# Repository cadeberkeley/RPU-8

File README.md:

# RPU-8
8-Bit Retro Processing Unit

Started on breadboards, inspired by Ben Eater's 8-bit CPU.  I got it more or less working on breadboards, and I am currently designing PCBs to make it more permanent and hopefully solve any power distribution or connection issues with the breadboard design.  I have sketched out a modular stacking design, so it will be easier to swap out for larger instruction/data memory or a larger program counter if I so please.

I am using KiCAD for schematic and PCB design.  Planning to source PCBs from JLCPCB.

TODO: Add images of breadboard.

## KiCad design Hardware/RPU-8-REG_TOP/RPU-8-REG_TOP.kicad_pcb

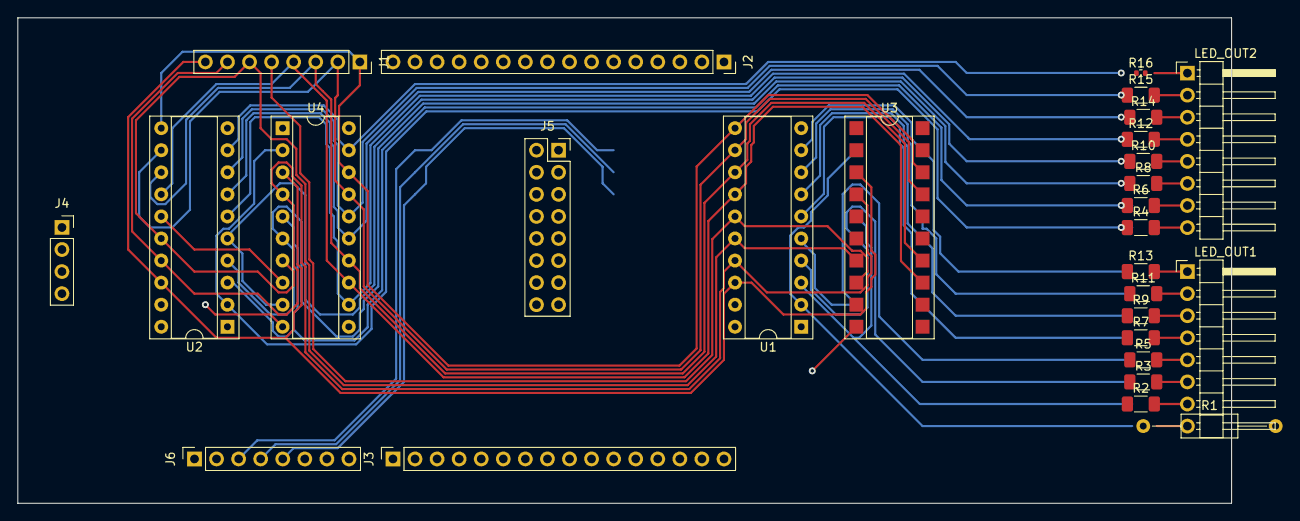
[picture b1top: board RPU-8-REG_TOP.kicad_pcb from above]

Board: 2 copper layers, 139.7 x 55.9 mm, 28 parts (0 on the bottom side), 47 nets.

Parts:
J1: DATA_BUS; PinSocket_1x08_P2.54mm_Vertical
J2: ADDR_BUS; PinSocket_1x16_P2.54mm_Vertical
J3: CTRL_BUS; PinSocket_1x16_P2.54mm_Vertical
J4: Conn_01x03_Female; PinSocket_1x04_P2.54mm_Vertical
J5: REG_CTRL; PinSocket_2x08_P2.54mm_Vertical
J6: INST_BITS; PinSocket_1x08_P2.54mm_Vertical
LED_OUT1, LED_OUT2: LEDs; PinHeader_1x08_P2.54mm_Horizontal
R1: 220Ω; R_Axial_DIN0207_L6.3mm_D2.5mm_P15.24mm_Horizontal
R2, R3, R4, R5, R6, R7, R8, R9, R10, R11, R12, R13, R14, R15: 220Ω; R_1206_3216Metric_Pad1.30x1.75mm_HandSolder
R16: 220Ω; R_0402_1005Metric
U1, U2: 74HC245; DIP-20_W7.62mm_Socket
U3: 74HC377; DIP-20_W7.62mm_SMDSocket_SmallPads
U4: 74HC377; DIP-20_W7.62mm_Socket

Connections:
+5V: J4.3, U1.1 (A->B), U1.20 (VCC), U2.1 (A->B), U2.20 (VCC), U3.20 (VCC), U4.20 (VCC)
CLK: J4.1, U3.11 (CP), U4.11 (CP)
D0: J1.1, U1.11 (B7), U2.11 (B7), U3.18 (D7), U4.18 (D7)
D1: J1.2, U1.12 (B6), U2.12 (B6), U3.17 (D6), U4.17 (D6)
D2: J1.3, U1.13 (B5), U2.13 (B5), U3.14 (D5), U4.14 (D5)
D3: J1.4, U1.14 (B4), U2.14 (B4), U3.13 (D4), U4.13 (D4)
D4: J1.5, U1.15 (B3), U2.15 (B3), U3.8 (D3), U4.8 (D3)
D5: J1.6, U1.16 (B2), U2.16 (B2), U3.7 (D2), U4.7 (D2)
D6: J1.7, U1.17 (B1), U2.17 (B1), U3.4 (D1), U4.4 (D1)
D7: J1.8, U1.18 (B0), U2.18 (B0), U3.3 (D0), U4.3 (D0)
GND: J4.2, U1.10 (GND), U2.10 (GND), U3.10 (GND), U4.10 (GND)
unnamed: LED_OUT1.1 (R0), R13.2
unnamed: LED_OUT1.2 (R1), R11.2
unnamed: LED_OUT1.3 (R2), R9.2
unnamed: LED_OUT1.4 (R3), R7.2
unnamed: LED_OUT1.5 (R4), R5.2
unnamed: LED_OUT1.6 (R5), R3.2
unnamed: LED_OUT1.7 (R6), R2.2
unnamed: LED_OUT1.8 (R7), R1.2
unnamed: LED_OUT2.1 (R0), R16.2
unnamed: LED_OUT2.2 (R1), R15.2
unnamed: LED_OUT2.3 (R2), R14.2
unnamed: LED_OUT2.4 (R3), R12.2
unnamed: LED_OUT2.5 (R4), R10.2
unnamed: LED_OUT2.6 (R5), R8.2
unnamed: LED_OUT2.7 (R6), R6.2
unnamed: LED_OUT2.8 (R7), R4.2
unnamed: R1.1, U1.2 (A0), U3.2 (Q0)
unnamed: R2.1, U1.3 (A1), U3.5 (Q1)
unnamed: R3.1, U1.4 (A2), U3.6 (Q2)
unnamed: R4.1, U2.2 (A0), U4.2 (Q0)
unnamed: R5.1, U1.5 (A3), U3.9 (Q3)
unnamed: R6.1, U2.3 (A1), U4.5 (Q1)
unnamed: R7.1, U1.6 (A4), U3.12 (Q4)
unnamed: R8.1, U2.4 (A2), U4.6 (Q2)
unnamed: R9.1, U1.7 (A5), U3.15 (Q5)
unnamed: R10.1, U2.5 (A3), U4.9 (Q3)
unnamed: R11.1, U1.8 (A6), U3.16 (Q6)
unnamed: R12.1, U2.6 (A4), U4.12 (Q4)
unnamed: R13.1, U1.9 (A7), U3.19 (Q7)
unnamed: R14.1, U2.7 (A5), U4.15 (Q5)
unnamed: R15.1, U2.8 (A6), U4.16 (Q6)
unnamed: R16.1, U2.9 (A7), U4.19 (Q7)
~R0_IN: J5.1, U3.1 (~E)
~R0_OUT: J5.2, U1.19 (CE)
~R1_IN: J5.3, U4.1 (~E)
~R1_OUT: J5.4, U2.19 (CE)

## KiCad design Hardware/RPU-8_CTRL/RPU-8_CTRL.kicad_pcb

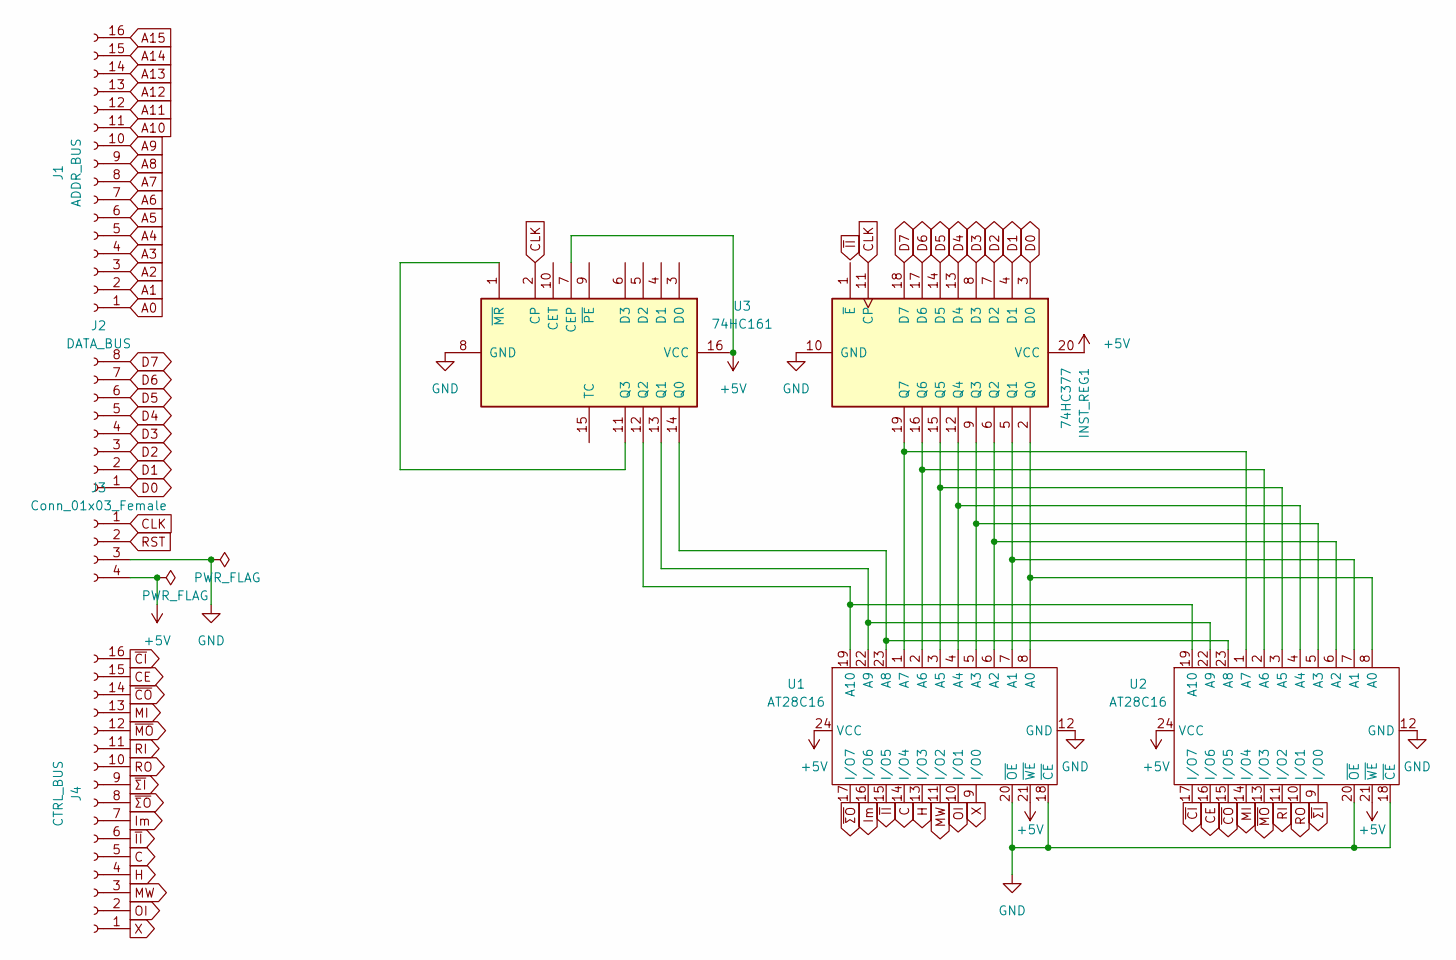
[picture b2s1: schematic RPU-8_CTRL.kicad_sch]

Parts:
INST_REG1: 74HC377; DIP-20_W7.62mm_Socket
J1: ADDR_BUS; PinSocket_1x16_P2.54mm_Vertical
J2: DATA_BUS; PinSocket_1x08_P2.54mm_Vertical
J3: Conn_01x03_Female; PinSocket_1x04_P2.54mm_Vertical
J4: CTRL_BUS; PinSocket_1x16_P2.54mm_Vertical
U1, U2: AT28C16; DIP-24_W15.24mm_Socket
U3: 74HC161; DIP-16_W7.62mm_Socket

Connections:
+5V: INST_REG1.20 (VCC), J3.4, U1.21 (~WE), U1.24 (VCC), U2.21 (~WE), U2.24 (VCC), U3.7 (CEP), U3.16 (VCC)
A0: J1.1
A1: J1.2
A2: J1.3
A3: J1.4
A4: J1.5
A5: J1.6
A6: J1.7
A7: J1.8
A8: J1.9
A9: J1.10
A10: J1.11
A11: J1.12
A12: J1.13
A13: J1.14
A14: J1.15
A15: J1.16
C: J4.5, U1.14 (I/O4)
CE: J4.15, U2.16 (I/O6)
CLK: INST_REG1.11 (CP), J3.1, U3.2 (CP)
D0: INST_REG1.3 (D0), J2.1
D1: INST_REG1.4 (D1), J2.2
D2: INST_REG1.7 (D2), J2.3
D3: INST_REG1.8 (D3), J2.4
D4: INST_REG1.13 (D4), J2.5
D5: INST_REG1.14 (D5), J2.6
D6: INST_REG1.17 (D6), J2.7
D7: INST_REG1.18 (D7), J2.8
GND: INST_REG1.10 (GND), J3.3, U1.12 (GND), U1.18 (~CE), U1.20 (~OE), U2.12 (GND), U2.18 (~CE), U2.20 (~OE), U3.8 (GND)
H: J4.4, U1.13 (I/O3)
Im: J4.7, U1.16 (I/O6)
MI: J4.13, U2.14 (I/O4)
MW: J4.3, U1.11 (I/O2)
unnamed: INST_REG1.19 (Q7), U1.1 (A7), U2.1 (A7)
unnamed: INST_REG1.16 (Q6), U1.2 (A6), U2.2 (A6)
unnamed: INST_REG1.15 (Q5), U1.3 (A5), U2.3 (A5)
unnamed: INST_REG1.12 (Q4), U1.4 (A4), U2.4 (A4)
unnamed: INST_REG1.9 (Q3), U1.5 (A3), U2.5 (A3)
unnamed: INST_REG1.6 (Q2), U1.6 (A2), U2.6 (A2)
unnamed: INST_REG1.5 (Q1), U1.7 (A1), U2.7 (A1)
unnamed: INST_REG1.2 (Q0), U1.8 (A0), U2.8 (A0)
unnamed: U1.22 (A9), U2.22 (A9), U3.13 (Q1)
unnamed: U1.23 (A8), U2.23 (A8), U3.14 (Q0)
unnamed: U1.19 (A10), U2.19 (A10), U3.12 (Q2)
unnamed: U3.1 (~MR), U3.11 (Q3)
OI: J4.2, U1.10 (I/O1)
RI: J4.11, U2.11 (I/O2)
RO: J4.10, U2.10 (I/O1)
RST: J3.2
X: J4.1, U1.9 (I/O0)
~CI: J4.16, U2.17 (I/O7)
~CO: J4.14, U2.15 (I/O5)
~II: J4.6, U1.15 (I/O5)
~MO: J4.12, U2.13 (I/O3)
~ΣI: J4.9, U2.9 (I/O0)
~ΣO: J4.8, U1.17 (I/O7)

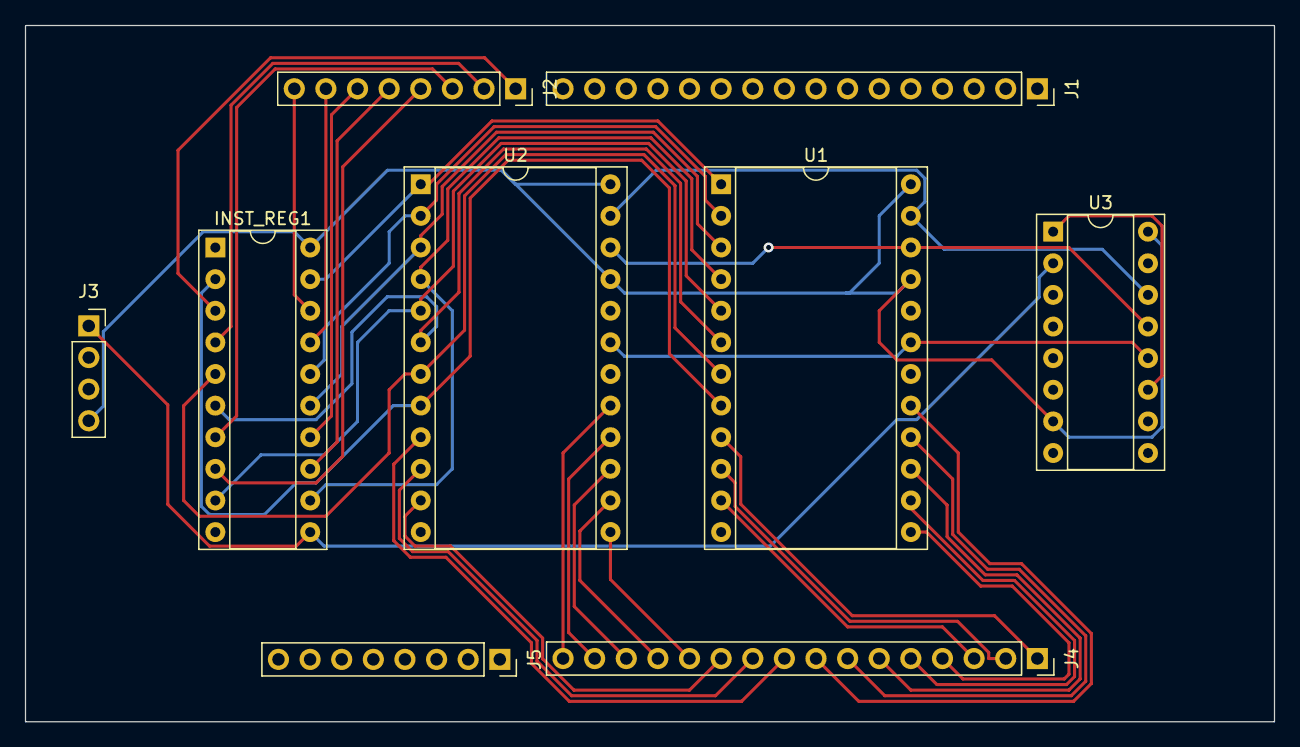
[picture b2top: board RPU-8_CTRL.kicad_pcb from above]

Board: 2 copper layers, 100.3 x 55.9 mm, 9 parts (0 on the bottom side), 39 nets.

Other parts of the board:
J5: INST_REG; PinSocket_1x08_P2.54mm_Vertical

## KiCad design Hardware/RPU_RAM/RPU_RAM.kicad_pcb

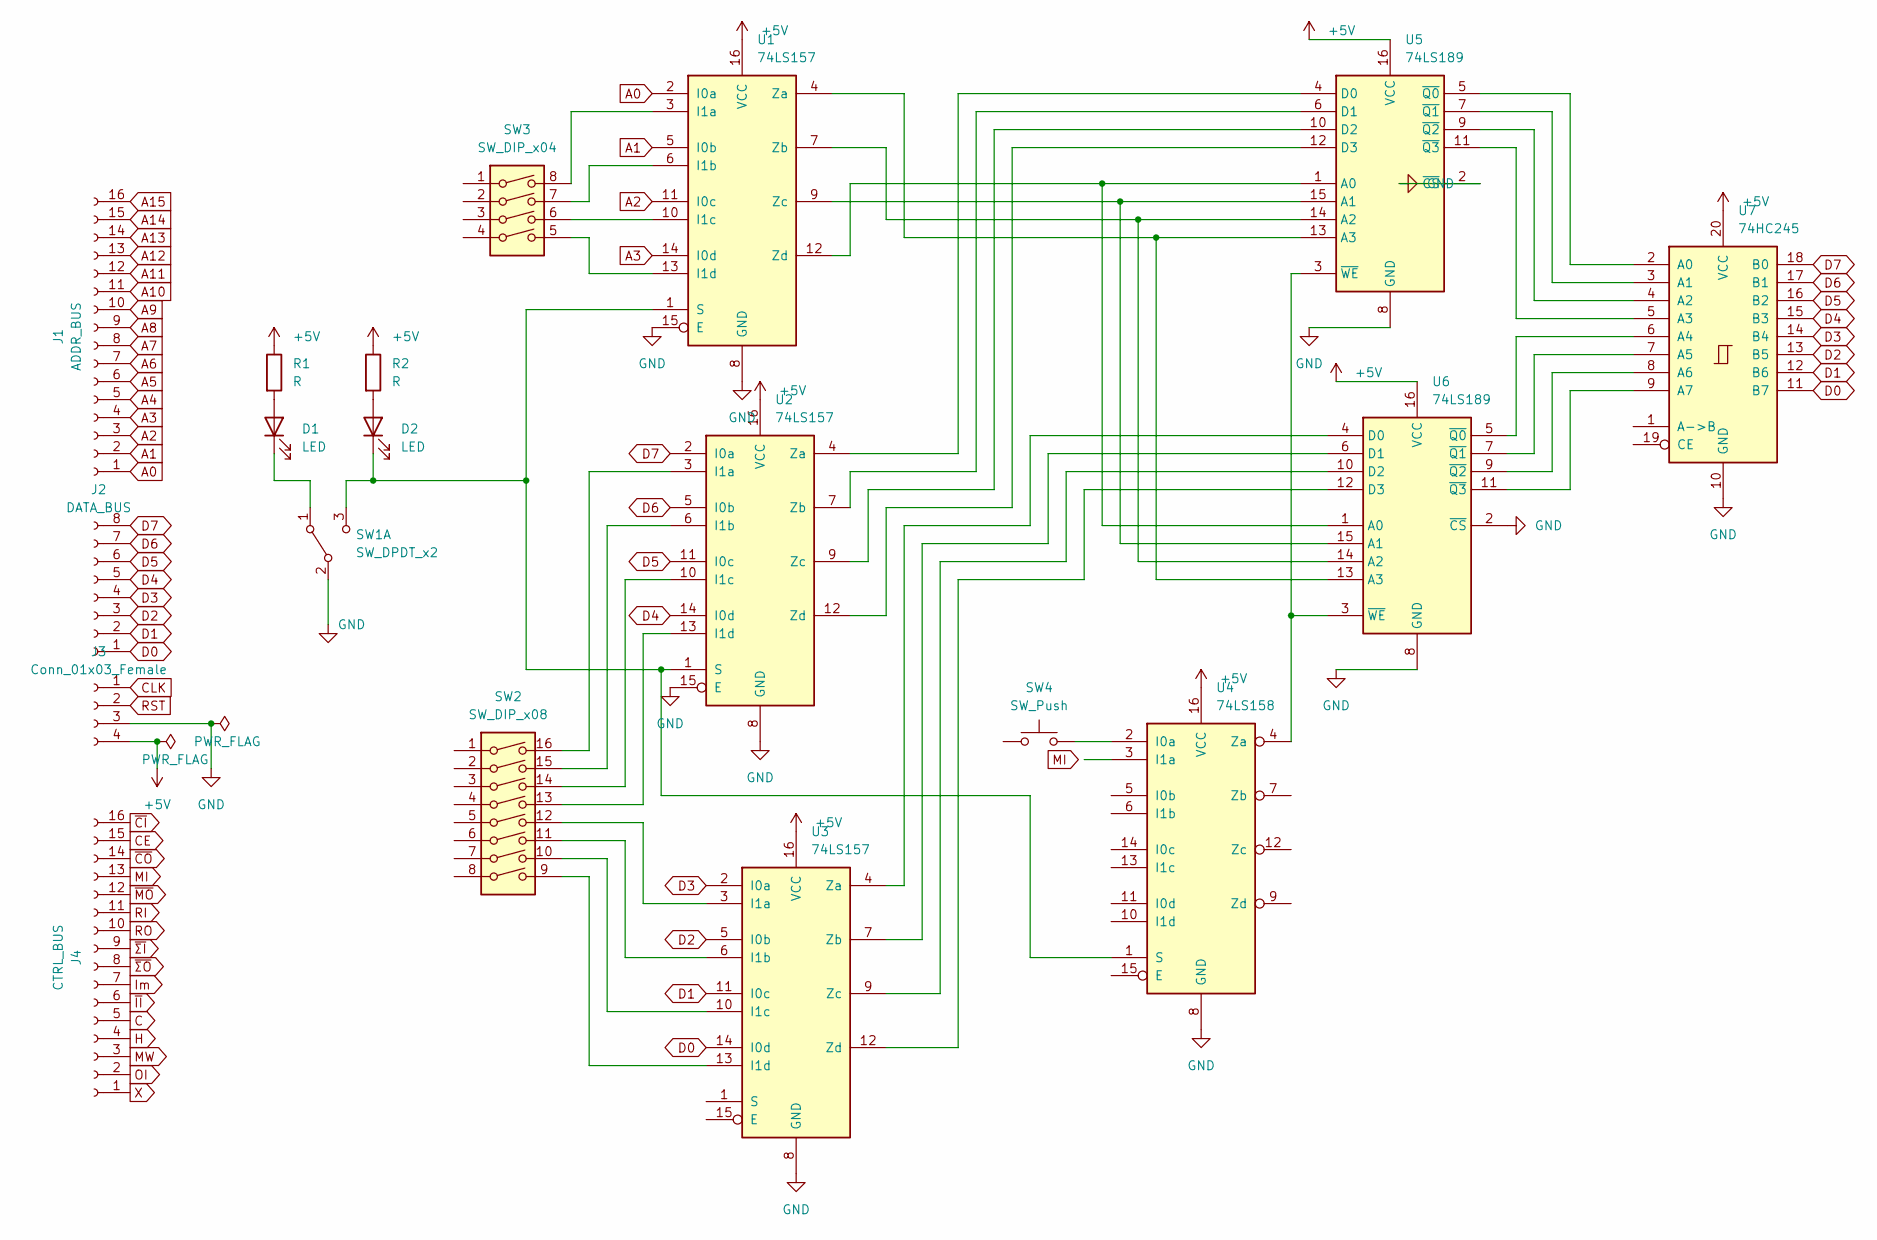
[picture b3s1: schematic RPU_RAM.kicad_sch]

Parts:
D1, D2: LED; LED_D3.0mm_Horizontal_O1.27mm_Z2.0mm
J1: ADDR_BUS; PinSocket_1x16_P2.54mm_Vertical
J2: DATA_BUS; PinSocket_1x08_P2.54mm_Vertical
J3: Conn_01x03_Female; PinSocket_1x04_P2.54mm_Vertical
J4: CTRL_BUS; PinSocket_1x16_P2.54mm_Vertical
R1, R2: R; R_0402_1005Metric
SW1: SW_DPDT_x2; SW_PUSH_6mm
SW2: SW_DIP_x08; DIP-16_W7.62mm
SW3: SW_DIP_x04; DIP-8_W7.62mm
SW4: SW_Push; SW_Slide_1P2T_CK_OS102011MS2Q
U1, U2, U3: 74LS157; DIP-16_W7.62mm
U4: 74LS158; DIP-16_W7.62mm
U5, U6: 74LS189; DIP-16_W7.62mm
U7: 74HC245; DIP-20_W7.62mm

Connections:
+5V: J3.4, R1.1, R2.1, U1.16 (VCC), U2.16 (VCC), U3.16 (VCC), U4.16 (VCC), U5.16 (VCC), U6.16 (VCC), U7.20 (VCC)
A0: J1.1, U1.2 (I0a)
A1: J1.2, U1.5 (I0b)
A2: J1.3, U1.11 (I0c)
A3: J1.4, U1.14 (I0d)
A4: J1.5
A5: J1.6
A6: J1.7
A7: J1.8
A8: J1.9
A9: J1.10
A10: J1.11
A11: J1.12
A12: J1.13
A13: J1.14
A14: J1.15
A15: J1.16
C: J4.5
CE: J4.15
CLK: J3.1
D0: J2.1, U3.14 (I0d), U7.11 (B7)
D1: J2.2, U3.11 (I0c), U7.12 (B6)
D2: J2.3, U3.5 (I0b), U7.13 (B5)
D3: J2.4, U3.2 (I0a), U7.14 (B4)
D4: J2.5, U2.14 (I0d), U7.15 (B3)
D5: J2.6, U2.11 (I0c), U7.16 (B2)
D6: J2.7, U2.5 (I0b), U7.17 (B1)
D7: J2.8, U2.2 (I0a), U7.18 (B0)
GND: J3.3, SW1.2 (B), U1.8 (GND), U1.15 (E), U2.8 (GND), U2.15 (E), U3.8 (GND), U4.8 (GND), U5.2 (~CS), U5.8 (GND), U6.2 (~CS), U6.8 (GND), U7.10 (GND)
H: J4.4
Im: J4.7
MI: J4.13
MW: J4.3
unnamed: D1.1 (K), SW1.1 (A)
unnamed: D1.2 (A), R1.2
unnamed: D2.1 (K), SW1.3 (C), U1.1 (S), U2.1 (S), U4.1 (S)
unnamed: D2.2 (A), R2.2
unnamed: SW2.9, U3.13 (I1d)
unnamed: SW2.10, U3.10 (I1c)
unnamed: SW2.11, U3.6 (I1b)
unnamed: SW2.12, U3.3 (I1a)
unnamed: SW2.13, U2.13 (I1d)
unnamed: SW2.14, U2.10 (I1c)
unnamed: SW2.15, U2.6 (I1b)
unnamed: SW2.16, U2.3 (I1a)
unnamed: SW3.5, U1.13 (I1d)
unnamed: SW3.6, U1.10 (I1c)
unnamed: SW3.7, U1.6 (I1b)
unnamed: SW3.8, U1.3 (I1a)
unnamed: SW4.2, U4.2 (I0a)
unnamed: U1.4 (Za), U5.13 (A3), U6.13 (A3)
unnamed: U1.7 (Zb), U5.14 (A2), U6.14 (A2)
unnamed: U1.9 (Zc), U5.15 (A1), U6.15 (A1)
unnamed: U1.12 (Zd), U5.1 (A0), U6.1 (A0)
unnamed: U2.4 (Za), U5.4 (D0)
unnamed: U2.7 (Zb), U5.6 (D1)
unnamed: U2.9 (Zc), U5.10 (D2)
unnamed: U2.12 (Zd), U5.12 (D3)
unnamed: U3.4 (Za), U6.4 (D0)
unnamed: U3.7 (Zb), U6.6 (D1)
unnamed: U3.9 (Zc), U6.10 (D2)
unnamed: U3.12 (Zd), U6.12 (D3)
unnamed: U4.4 (Za), U5.3 (~WE), U6.3 (~WE)
unnamed: U5.5 (~Q0), U7.2 (A0)
unnamed: U5.7 (~Q1), U7.3 (A1)
unnamed: U5.9 (~Q2), U7.4 (A2)
unnamed: U5.11 (~Q3), U7.5 (A3)
unnamed: U6.5 (~Q0), U7.6 (A4)
unnamed: U6.7 (~Q1), U7.7 (A5)
unnamed: U6.9 (~Q2), U7.8 (A6)
unnamed: U6.11 (~Q3), U7.9 (A7)
OI: J4.2
RI: J4.11
RO: J4.10
RST: J3.2
X: J4.1
~CI: J4.16
~CO: J4.14
~II: J4.6
~MO: J4.12
~ΣI: J4.9
~ΣO: J4.8

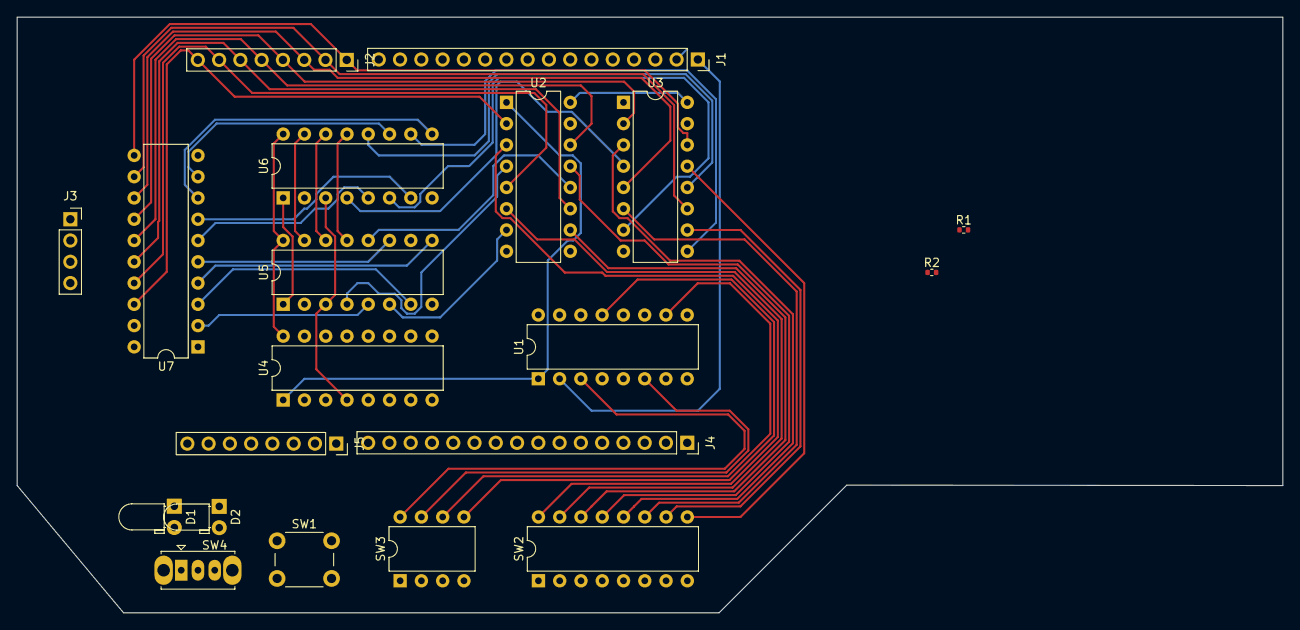
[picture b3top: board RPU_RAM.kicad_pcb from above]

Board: 2 copper layers, 151.1 x 71.1 mm, 20 parts (0 on the bottom side), 52 nets.

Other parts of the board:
J5: INST_REG; PinSocket_1x08_P2.54mm_Vertical

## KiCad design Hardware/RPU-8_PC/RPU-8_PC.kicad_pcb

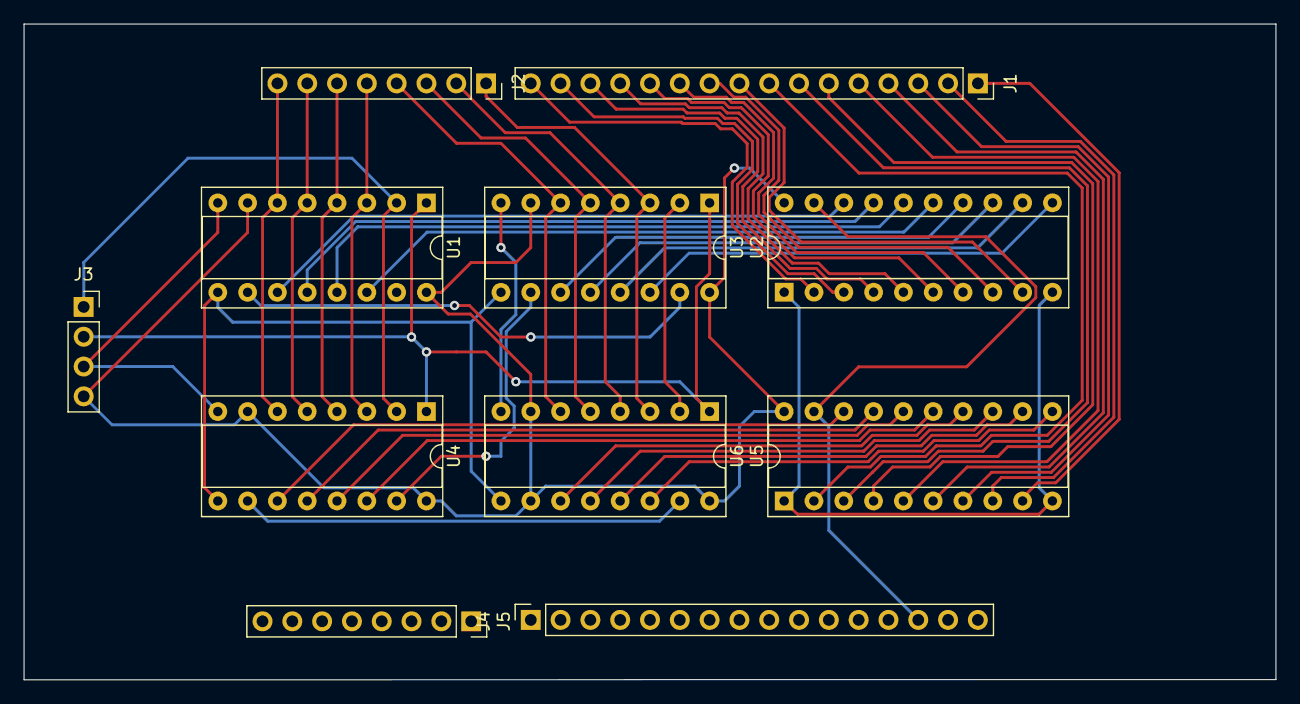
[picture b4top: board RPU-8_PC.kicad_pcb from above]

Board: 2 copper layers, 106.7 x 55.9 mm, 11 parts (0 on the bottom side), 49 nets.

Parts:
J1: ADDR_BUS; PinSocket_1x16_P2.54mm_Vertical
J2: DATA_BUS; PinSocket_1x08_P2.54mm_Vertical
J3: Conn_01x03_Female; PinSocket_1x04_P2.54mm_Vertical
J4: CTRL_BUS; PinSocket_1x16_P2.54mm_Vertical
J5: INST_REG; PinSocket_1x08_P2.54mm_Vertical
U1, U3, U4, U6: 74HC161; DIP-16_W7.62mm_Socket
U2, U5: 74HC245; DIP-20_W7.62mm_Socket

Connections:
+5V: J3.4, U1.7 (CEP), U1.16 (VCC), U2.20 (VCC), U3.7 (CEP), U3.16 (VCC), U4.7 (CEP), U4.16 (VCC), U5.20 (VCC), U6.7 (CEP), U6.10 (CET), U6.16 (VCC)
A0: J1.1, U5.9 (A7)
A1: J1.2, U5.8 (A6)
A2: J1.3, U5.7 (A5)
A3: J1.4, U5.6 (A4)
A4: J1.5, U5.5 (A3)
A5: J1.6, U5.4 (A2)
A6: J1.7, U5.3 (A1)
A7: J1.8, U5.2 (A0)
A8: J1.9, U2.9 (A7)
A9: J1.10, U2.8 (A6)
A10: J1.11, U2.7 (A5)
A11: J1.12, U2.6 (A4)
A12: J1.13, U2.5 (A3)
A13: J1.14, U2.4 (A2)
A14: J1.15, U2.3 (A1)
A15: J1.16, U2.2 (A0)
CLK: J3.1, U1.2 (CP), U3.2 (CP), U4.2 (CP), U6.2 (CP)
D0: J2.1, U3.3 (D0), U6.3 (D0)
D1: J2.2, U3.4 (D1), U6.4 (D1)
D2: J2.3, U3.5 (D2), U6.5 (D2)
D3: J2.4, U3.6 (D3), U6.6 (D3)
D4: J2.5, U1.3 (D0), U4.3 (D0)
D5: J2.6, U1.4 (D1), U4.4 (D1)
D6: J2.7, U1.5 (D2), U4.5 (D2)
D7: J2.8, U1.6 (D3), U4.6 (D3)
GND: J3.3, U1.8 (GND), U2.1 (A->B), U2.10 (GND), U3.8 (GND), U4.8 (GND), U5.1 (A->B), U5.10 (GND), U6.8 (GND)
unnamed: U1.10 (CET), U3.15 (TC)
unnamed: U1.11 (Q3), U2.18 (B0)
unnamed: U1.12 (Q2), U2.17 (B1)
unnamed: U1.13 (Q1), U2.16 (B2)
unnamed: U1.14 (Q0), U2.15 (B3)
unnamed: U2.11 (B7), U3.14 (Q0)
unnamed: U2.12 (B6), U3.13 (Q1)
unnamed: U2.13 (B5), U3.12 (Q2)
unnamed: U2.14 (B4), U3.11 (Q3)
unnamed: U3.10 (CET), U4.15 (TC)
unnamed: U4.10 (CET), U6.15 (TC)
unnamed: U4.11 (Q3), U5.18 (B0)
unnamed: U4.12 (Q2), U5.17 (B1)
unnamed: U4.13 (Q1), U5.16 (B2)
unnamed: U4.14 (Q0), U5.15 (B3)
unnamed: U5.11 (B7), U6.14 (Q0)
unnamed: U5.12 (B6), U6.13 (Q1)
unnamed: U5.13 (B5), U6.12 (Q2)
unnamed: U5.14 (B4), U6.11 (Q3)
RST: J3.2, U1.1 (~MR), U3.1 (~MR), U4.1 (~MR), U6.1 (~MR)
~CIL: U1.9 (~PE), U3.9 (~PE), U4.9 (~PE), U6.9 (~PE)
~CO: J4.14, U2.19 (CE), U5.19 (CE)

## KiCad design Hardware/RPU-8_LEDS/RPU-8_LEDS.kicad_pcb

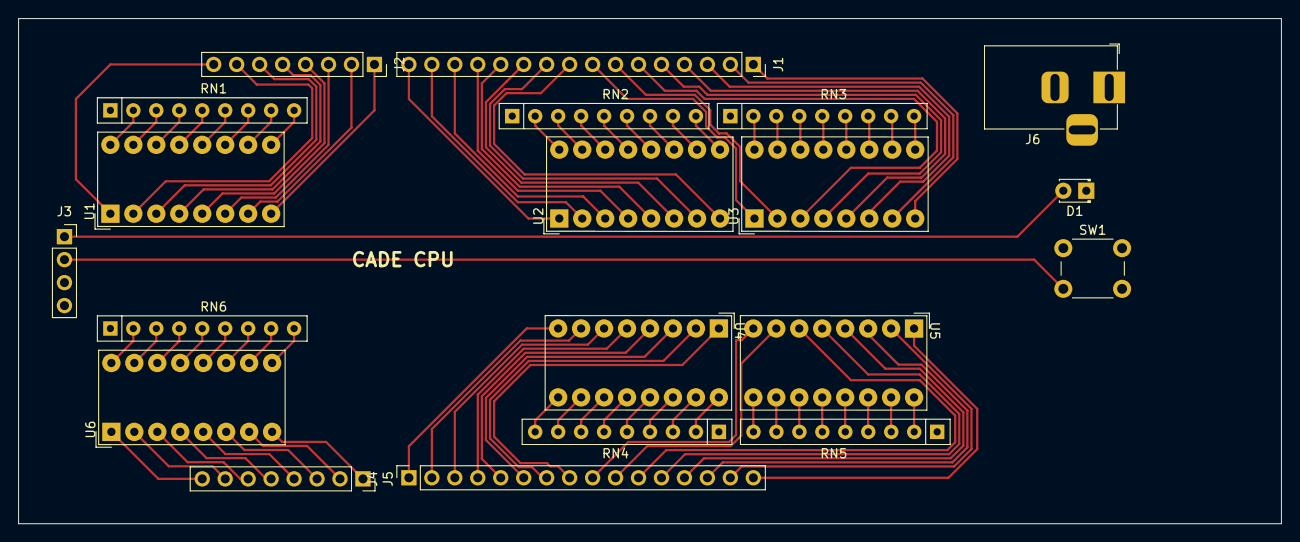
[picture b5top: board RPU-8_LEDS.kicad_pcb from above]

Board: 4 copper layers, 139.7 x 55.9 mm, 20 parts (0 on the bottom side), 100 nets.

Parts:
D1: LED; LED_D1.8mm_W3.3mm_H2.4mm
J1: ADDR_BUS; PinSocket_1x16_P2.54mm_Vertical
J2: DATA_BUS; PinSocket_1x08_P2.54mm_Vertical
J3: Conn_01x03_Female; PinSocket_1x04_P2.54mm_Vertical
J4: CTRL_BUS; PinSocket_1x16_P2.54mm_Vertical
J5: INST_REG; PinSocket_1x08_P2.54mm_Vertical
J6: Barrel_Jack; BarrelJack_Horizontal
RN1, RN2, RN3, RN4, RN5, RN6: R_Network08; R_Array_SIP9
SW1: SW_Push; SW_PUSH_6mm
U1, U2, U3, U4, U5, U6: 8_Segment_LED_Bar_Graph; 8-SEGMENT_LED

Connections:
+5V: J3.4, J6.2, SW1.1
A0: J1.1, U3.8 (A)
A1: J1.2, U3.7 (A)
A2: J1.3, U3.6 (A)
A3: J1.4, U3.5 (A)
A4: J1.5, U3.4 (A)
A5: J1.6, U3.3 (A)
A6: J1.7, U3.2 (A)
A7: J1.8, U3.1 (A)
A8: J1.9, U2.8 (A)
A9: J1.10, U2.7 (A)
A10: J1.11, U2.6 (A)
A11: J1.12, U2.5 (A)
A12: J1.13, U2.4 (A)
A13: J1.14, U2.3 (A)
A14: J1.15, U2.2 (A)
A15: J1.16, U2.1 (A)
C: J4.5, U4.4 (A)
CE: J4.15, U5.2 (A)
CLK: D1.2 (A), J3.1
D0: J2.1, U1.8 (A)
D1: J2.2, U1.7 (A)
D2: J2.3, U1.6 (A)
D3: J2.4, U1.5 (A)
D4: J2.5, U1.4 (A)
D5: J2.6, U1.3 (A)
D6: J2.7, U1.2 (A)
D7: J2.8, U1.1 (A)
GND: D1.1 (K), J3.3, J6.1, RN1.1 (common), RN2.1 (common), RN3.1 (common), RN4.1 (common), RN5.1 (common), RN6.1 (common)
H: J4.4, U4.5 (A)
I0: J5.1, U6.8 (A)
I1: J5.2, U6.7 (A)
I3: J5.3, U6.6 (A)
I4: J5.4, U6.5 (A)
I5: J5.5, U6.4 (A)
I6: J5.6, U6.3 (A)
I7: J5.7, U6.2 (A)
I8: J5.8, U6.1 (A)
Im: J4.7, U4.2 (A)
MI: J4.13, U5.4 (A)
MW: J4.3, U4.6 (A)
unnamed: RN1.2 (R1), U1.16 (K)
unnamed: RN1.3 (R2), U1.15 (K)
unnamed: RN1.4 (R3), U1.14 (K)
unnamed: RN1.5 (R4), U1.13 (K)
unnamed: RN1.6 (R5), U1.12 (K)
unnamed: RN1.7 (R6), U1.11 (K)
unnamed: RN1.8 (R7), U1.10 (K)
unnamed: RN1.9 (R8), U1.9 (K)
unnamed: RN2.2 (R1), U2.16 (K)
unnamed: RN2.3 (R2), U2.15 (K)
unnamed: RN2.4 (R3), U2.14 (K)
unnamed: RN2.5 (R4), U2.13 (K)
unnamed: RN2.6 (R5), U2.12 (K)
unnamed: RN2.7 (R6), U2.11 (K)
unnamed: RN2.8 (R7), U2.10 (K)
unnamed: RN2.9 (R8), U2.9 (K)
unnamed: RN3.2 (R1), U3.16 (K)
unnamed: RN3.3 (R2), U3.15 (K)
unnamed: RN3.4 (R3), U3.14 (K)
unnamed: RN3.5 (R4), U3.13 (K)
unnamed: RN3.6 (R5), U3.12 (K)
unnamed: RN3.7 (R6), U3.11 (K)
unnamed: RN3.8 (R7), U3.10 (K)
unnamed: RN3.9 (R8), U3.9 (K)
unnamed: RN4.2 (R1), U4.16 (K)
unnamed: RN4.3 (R2), U4.15 (K)
unnamed: RN4.4 (R3), U4.14 (K)
unnamed: RN4.5 (R4), U4.13 (K)
unnamed: RN4.6 (R5), U4.12 (K)
unnamed: RN4.7 (R6), U4.11 (K)
unnamed: RN4.8 (R7), U4.10 (K)
unnamed: RN4.9 (R8), U4.9 (K)
unnamed: RN5.2 (R1), U5.16 (K)
unnamed: RN5.3 (R2), U5.15 (K)
unnamed: RN5.4 (R3), U5.14 (K)
unnamed: RN5.5 (R4), U5.13 (K)
unnamed: RN5.6 (R5), U5.12 (K)
unnamed: RN5.7 (R6), U5.11 (K)
unnamed: RN5.8 (R7), U5.10 (K)
unnamed: RN5.9 (R8), U5.9 (K)
unnamed: RN6.2 (R1), U6.16 (K)
unnamed: RN6.3 (R2), U6.15 (K)
unnamed: RN6.4 (R3), U6.14 (K)
unnamed: RN6.5 (R4), U6.13 (K)
unnamed: RN6.6 (R5), U6.12 (K)
unnamed: RN6.7 (R6), U6.11 (K)
unnamed: RN6.8 (R7), U6.10 (K)
unnamed: RN6.9 (R8), U6.9 (K)
OI: J4.2, U4.7 (A)
RI: J4.11, U5.6 (A)
RO: J4.10, U5.7 (A)
RST: J3.2, SW1.2
X: J4.1, U4.8 (A)
~CI: J4.16, U5.1 (A)
~CO: J4.14, U5.3 (A)
~II: J4.6, U4.3 (A)
~MO: J4.12, U5.5 (A)
~ΣI: J4.9, U5.8 (A)
~ΣO: J4.8, U4.1 (A)

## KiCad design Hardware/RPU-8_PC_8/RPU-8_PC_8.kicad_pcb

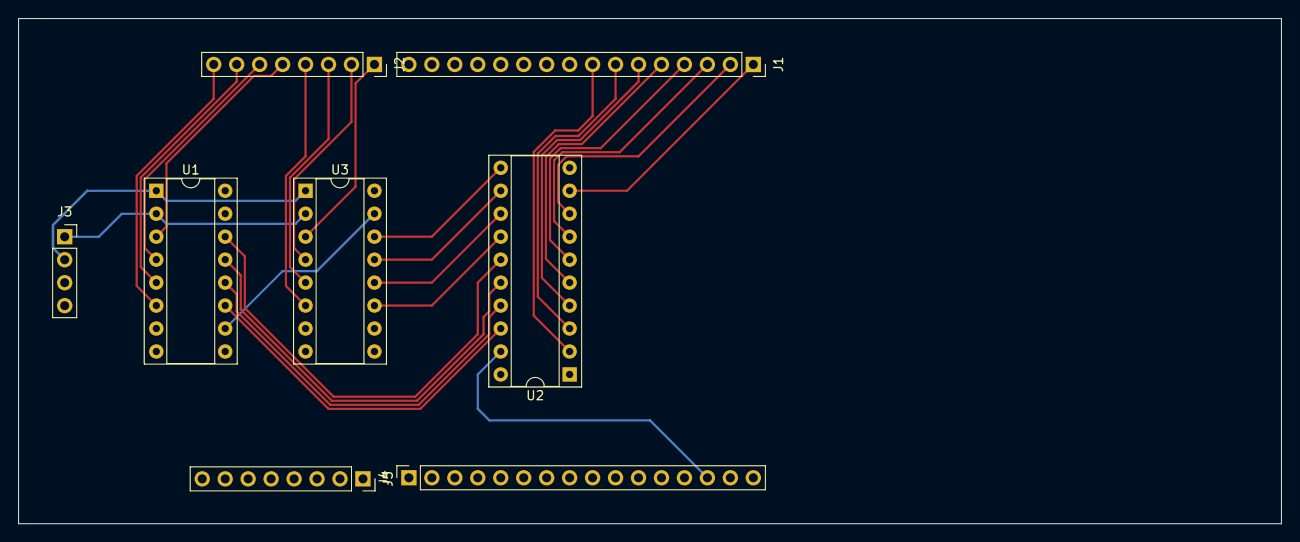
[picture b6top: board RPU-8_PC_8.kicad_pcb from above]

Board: 4 copper layers, 139.7 x 55.9 mm, 8 parts (0 on the bottom side), 31 nets.

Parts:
J1: ADDR_BUS; PinSocket_1x16_P2.54mm_Vertical
J2: DATA_BUS; PinSocket_1x08_P2.54mm_Vertical
J3: Conn_01x03_Female; PinSocket_1x04_P2.54mm_Vertical
J4: CTRL_BUS; PinSocket_1x16_P2.54mm_Vertical
J5: INST_REG; PinSocket_1x08_P2.54mm_Vertical
U1, U3: 74HC161; DIP-16_W7.62mm_Socket
U2: 74HC245; DIP-20_W7.62mm_Socket

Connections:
+5V: J3.4, U1.7 (CEP), U1.16 (VCC), U2.20 (VCC), U3.7 (CEP), U3.10 (CET), U3.16 (VCC)
A0: J1.1, U2.9 (A7)
A1: J1.2, U2.8 (A6)
A2: J1.3, U2.7 (A5)
A3: J1.4, U2.6 (A4)
A4: J1.5, U2.5 (A3)
A5: J1.6, U2.4 (A2)
A6: J1.7, U2.3 (A1)
A7: J1.8, U2.2 (A0)
CLK: J3.1, U1.2 (CP), U3.2 (CP)
D0: J2.1, U3.3 (D0)
D1: J2.2, U3.4 (D1)
D2: J2.3, U3.5 (D2)
D3: J2.4, U3.6 (D3)
D4: J2.5, U1.3 (D0)
D5: J2.6, U1.4 (D1)
D6: J2.7, U1.5 (D2)
D7: J2.8, U1.6 (D3)
GND: J3.3, U1.8 (GND), U2.1 (A->B), U2.10 (GND), U3.8 (GND)
unnamed: U1.10 (CET), U3.15 (TC)
unnamed: U1.11 (Q3), U2.18 (B0)
unnamed: U1.12 (Q2), U2.17 (B1)
unnamed: U1.13 (Q1), U2.16 (B2)
unnamed: U1.14 (Q0), U2.15 (B3)
unnamed: U2.11 (B7), U3.14 (Q0)
unnamed: U2.12 (B6), U3.13 (Q1)
unnamed: U2.13 (B5), U3.12 (Q2)
unnamed: U2.14 (B4), U3.11 (Q3)
RST: J3.2, U1.1 (~MR), U3.1 (~MR)
~CIL: U1.9 (~PE), U3.9 (~PE)
~CO: J4.14, U2.19 (CE)

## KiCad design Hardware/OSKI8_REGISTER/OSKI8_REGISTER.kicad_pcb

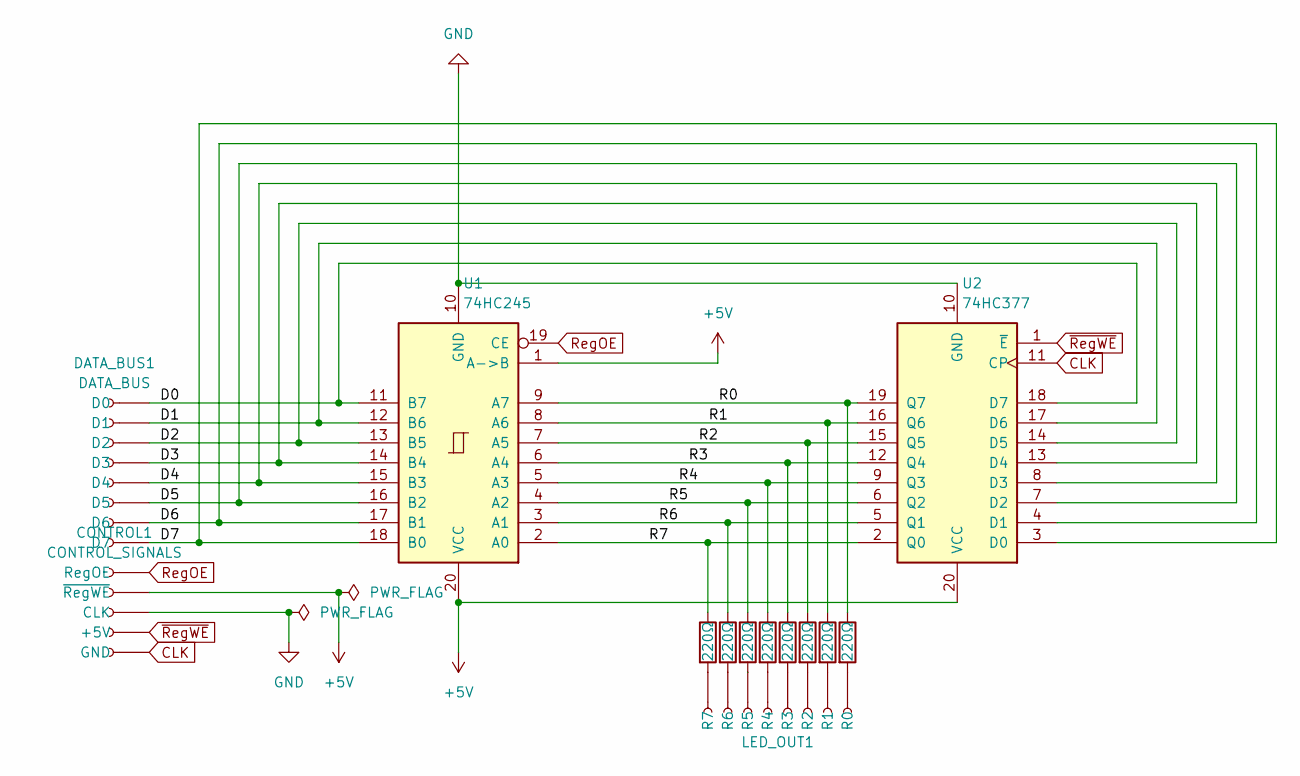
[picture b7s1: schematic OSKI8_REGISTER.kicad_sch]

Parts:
CONTROL1: CONTROL_SIGNALS; PinSocket_1x05_P2.54mm_Vertical
DATA_BUS1: DATA_BUS; PinSocket_1x08_P2.54mm_Vertical
LED_OUT1: LEDs; PinHeader_1x08_P2.54mm_Horizontal
R0, R1, R2, R3, R4, R5, R6, R7: 220Ω; R_1206_3216Metric_Pad1.30x1.75mm_HandSolder
U1: 74HC245; DIP-20_W7.62mm_Socket
U2: 74HC377; DIP-20_W7.62mm_Socket

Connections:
+5V: CONTROL1.2 (~RegWE), U1.1 (A->B), U1.20 (VCC), U2.20 (VCC)
/D0: DATA_BUS1.1 (D0), U1.11 (B7), U2.18 (D7)
/D1: DATA_BUS1.2 (D1), U1.12 (B6), U2.17 (D6)
/D2: DATA_BUS1.3 (D2), U1.13 (B5), U2.14 (D5)
/D3: DATA_BUS1.4 (D3), U1.14 (B4), U2.13 (D4)
/D4: DATA_BUS1.5 (D4), U1.15 (B3), U2.8 (D3)
/D5: DATA_BUS1.6 (D5), U1.16 (B2), U2.7 (D2)
/D6: DATA_BUS1.7 (D6), U1.17 (B1), U2.4 (D1)
/D7: DATA_BUS1.8 (D7), U1.18 (B0), U2.3 (D0)
/R0: R0.1, U1.9 (A7), U2.19 (Q7)
/R1: R7.1, U1.8 (A6), U2.16 (Q6)
/R2: R6.1, U1.7 (A5), U2.15 (Q5)
/R3: R5.1, U1.6 (A4), U2.12 (Q4)
/R4: R4.1, U1.5 (A3), U2.9 (Q3)
/R5: R3.1, U1.4 (A2), U2.6 (Q2)
/R6: R2.1, U1.3 (A1), U2.5 (Q1)
/R7: R1.1, U1.2 (A0), U2.2 (Q0)
CLK: CONTROL1.5 (GND), U2.11 (CP)
GND: CONTROL1.3 (CLK), U1.10 (GND), U2.10 (GND)
unnamed: LED_OUT1.1 (R0), R0.2
unnamed: LED_OUT1.2 (R1), R7.2
unnamed: LED_OUT1.3 (R2), R6.2
unnamed: LED_OUT1.4 (R3), R5.2
unnamed: LED_OUT1.5 (R4), R4.2
unnamed: LED_OUT1.6 (R5), R3.2
unnamed: LED_OUT1.7 (R6), R2.2
unnamed: LED_OUT1.8 (R7), R1.2
RegOE: CONTROL1.1 (RegOE), U1.19 (CE)
~RegWE: CONTROL1.4 (+5V), U2.1 (~E)

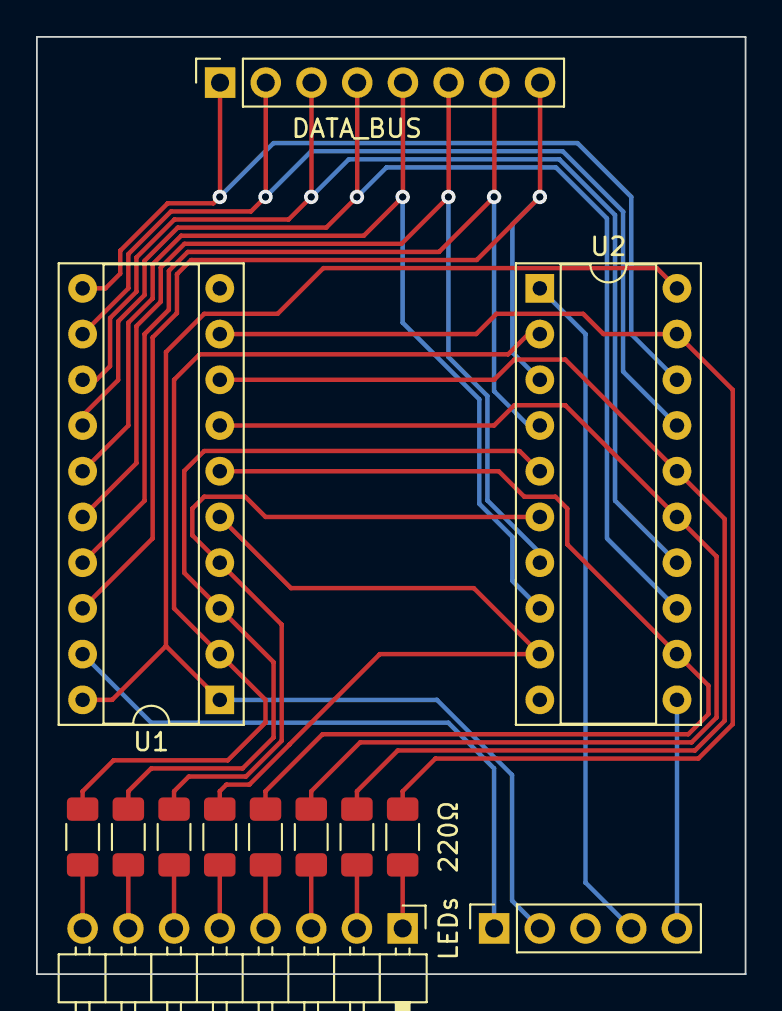
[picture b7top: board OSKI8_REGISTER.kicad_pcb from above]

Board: 2 copper layers, 39.4 x 52.1 mm, 13 parts (0 on the bottom side), 29 nets.

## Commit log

2022-12-22 Putting this on GitHub
2022-12-24 CTRL Board Layout Fixed
2022-12-24 new 8-bit PC, add 16-bit later
2022-12-24 fixed REG layout
2022-12-24 updated TODO.md
2024-01-14 added images
2024-01-17 add .readthedocs.yaml
